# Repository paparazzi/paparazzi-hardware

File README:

#
#   $Id: README 6372 2010-11-07 00:50:29Z esden $
#   Copyright (C) 2004 Pascal Brisset, Antoine Drouin
#
# This file is part of paparazzi.
#
# paparazzi is free software; you can redistribute it and/or modify
# it under the terms of the GNU General Public License as published by
# the Free Software Foundation; either version 2, or (at your option)
# any later version.
#
# paparazzi is distributed in the hope that it will be useful,
# but WITHOUT ANY WARRANTY; without even the implied warranty of
# MERCHANTABILITY or FITNESS FOR A PARTICULAR PURPOSE.  See the
# GNU General Public License for more details.
#
# You should have received a copy of the GNU General Public License
# along with paparazzi; see the file COPYING.  If not, write to
# the Free Software Foundation, 59 Temple Place - Suite 330,
# Boston, MA 02111-1307, USA.  
# 

License:
--------
All PCB CAD files are released under GNU General Public License version 2 or
newer if not stated otherwise.

Older revisions:
----------------
This is a cleaned up repository that does not contain all the history of the
files. For older revisions please check the SVN repository on Savannah:
http://svn.savannah.nongnu.org/viewvc/paparazzi-hardware/trunk/?root=paparazzi

Techno:
-------
PCBs are 4 layers boards.
  They can be ordered from companies like eurocircuits (www.eurocircuits.com).
  I solder the components with a fine temperatue controlled iron. The IMU board 
  contains BGA gyros which will require some sort hot hot air method.

Tools:
  This files are produced using Eagle (www.cadsoft.de) version 4.11 for Linux.
  gerbmerge (http://claymore.engineer.gvsu.edu/~steriana/Python/gerbmerge/) is a
  free gerber panelisation tool. gerbv (http://gerbv.sourceforge.net) is a free
  gerber viewer. eagle3d ( http://www.matwei.de/doku.php?id=en:eagle3d:eagle3d )
  is a tool that allows generation of povray views of the boards.

Outputs:
  We use the eagle batch CAM processor to generate various outputs.
  type "make gerber" to generate gerber.
  type "make printable" to generate postscript and pdf. 
  they will be put in a printable subdirectory in each subdirectory. 

Directory content:
------------------
panel: 
  Contains configuration files used in conjunction with gerbmerge to produce a pannel
  to be sent to the PCB manufacturer (eurocircuits). A panel is a big PCB containing several smaller PCB.
  It allows you to choose which boards you want for your particular system.

controller: 
  This are the paparazzi controller boards.

sensors:

tools:

lib: 
  contains eagle library parts for components not found in the standard eagle library.

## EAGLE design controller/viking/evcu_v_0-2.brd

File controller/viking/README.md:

# Viking Motorsports Engine Control Unit

The latest version is `ECU v1.0` which corresponds to `v_0.2` board files.  More info can be found in https://wiki.paparazziuav.org/wiki/VMS_ECU

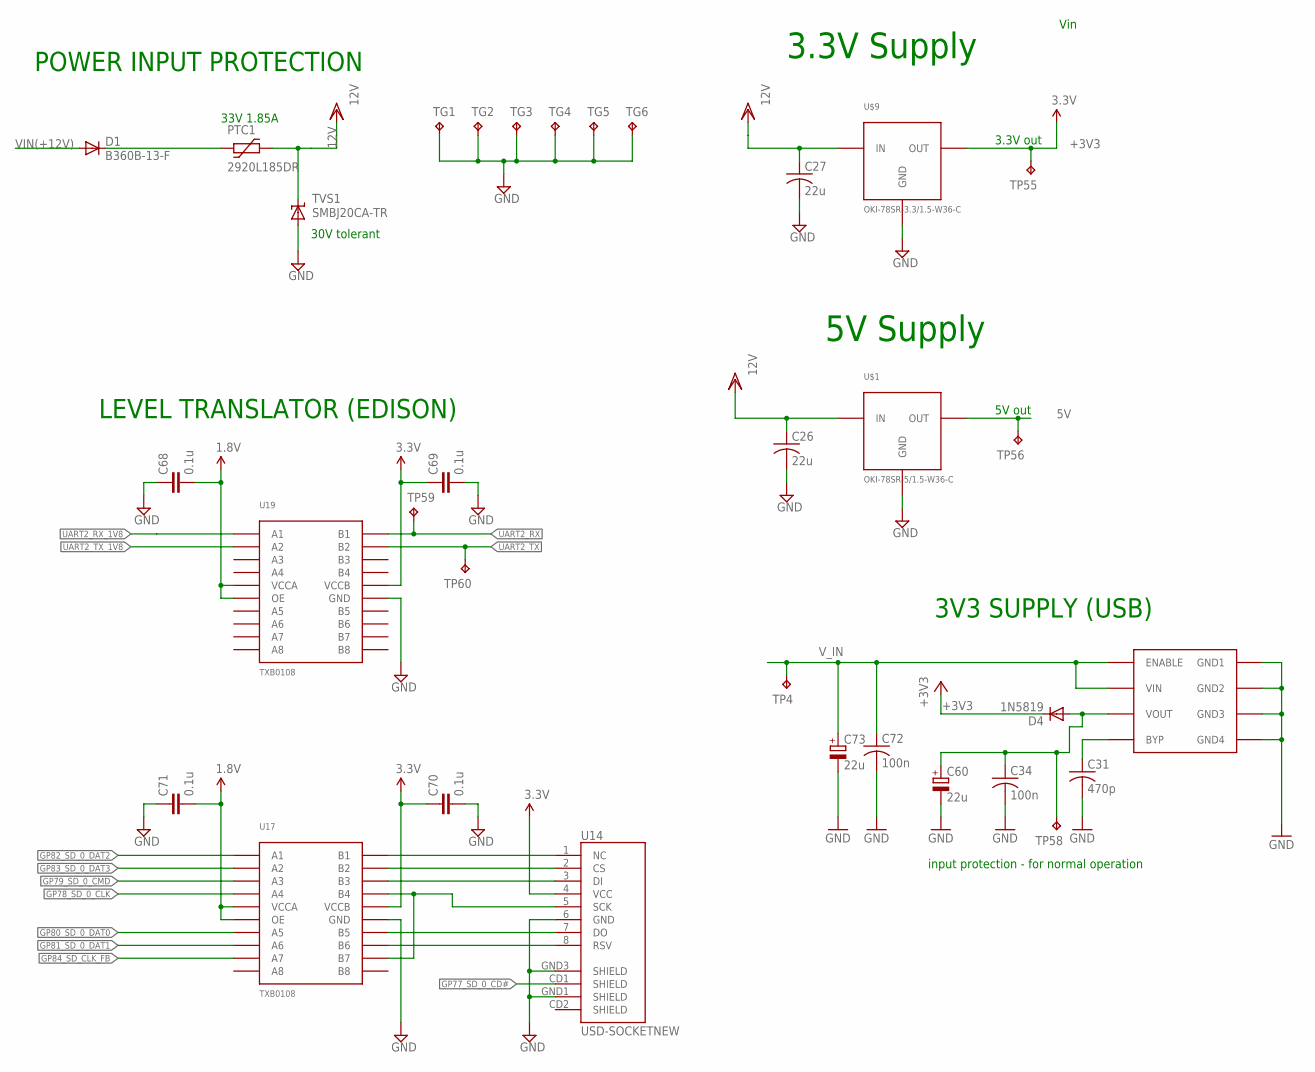
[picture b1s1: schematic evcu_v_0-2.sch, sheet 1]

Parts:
C26, C27: 22u; C1206
C31: 470p; C0603; PARTNO CC0402KRX7R9BB471
C34: 100n; C0603; PARTNO C0603C104K5RACTU
C60, C73: 22u; 3528/B; PARTNO T491B226M016AT
C68, C69, C70, C71: 0.1u; C0603@1
C72: 100n; C0603; PARTNO LMK105BJ104KV-F
D1: B360B-13-F; SMB
D4: 1N5819; MICROMELF-R; PARTNO RB160SS-40T2R
PTC1: 2920L185DR; 2920L
TG1, TG2, TG3, TG4, TG5, TG6: TPB1,27; B1,27
TP4, TP55, TP56, TP58, TP59, TP60: TPB1,27; B1,27
TVS1: SMBJ20CA-TR; SMBJ; PARTNO SM30T35AY
U14: USD-SOCKETNEW; MICRO-SD-SOCKET-PP
U17, U19: TXB0108; TSSOP20
U$1: OKI-78SR-5/1.5-W36-C; OKI-78SR
U$9: OKI-78SR-3.3/1.5-W36-C; OKI-78SR
VREG1: MIC5209; SOIC8; PARTNO MIC5209-3.3YM

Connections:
5V: TP56.TP, U$1.P3 (OUT); also elsewhere on the board
12V: C26.1, C27.1, PTC1.P$2 (2), TVS1.C, U$1.P1 (IN), U$9.P1 (IN); also elsewhere on the board
+1V8: C68.2, C71.2, U17.2 (VCCA), U17.10 (OE), U19.2 (VCCA), U19.10 (OE); also elsewhere on the board
+3V3: C69.1, C70.1, D4.C, TP55.TP, U14.4 (VCC), U17.19 (VCCB), U19.19 (VCCB), U$9.P3 (OUT); also elsewhere on the board
GND: C26.2, C27.2, C31.2, C34.2, C60.-, C68.1, C69.2, C70.2, C71.1, C72.2, C73.-, TG1.TP, TG2.TP, TG3.TP, TG4.TP, TG5.TP, TG6.TP, TVS1.A, U14.6 (GND), U14.GND1 (SHIELD), U14.GND3 (SHIELD), U17.11 (GND), U19.11 (GND), U$1.P2 (GND), U$9.P2 (GND), VREG1.5 (GND4), VREG1.6 (GND3), VREG1.7 (GND2), VREG1.8 (GND1); also elsewhere on the board
GP77_SD_0_CD#: U14.CD1 (SHIELD); also elsewhere on the board
GP78_SD_0_CLK: U17.5 (A4); also elsewhere on the board
GP79_SD_0_CMD: U17.4 (A3); also elsewhere on the board
GP80_SD_0_DAT0: U17.6 (A5); also elsewhere on the board
GP81_SD_0_DAT1: U17.7 (A6); also elsewhere on the board
GP82_SD_0_DAT2: U17.1 (A1); also elsewhere on the board
GP83_SD_0_DAT3: U17.3 (A2); also elsewhere on the board
GP84_SD_CLK_FB: U17.8 (A7); also elsewhere on the board
unnamed: U14.1 (NC), U17.20 (B1)
unnamed: U14.2 (CS), U17.18 (B2)
unnamed: U14.3 (DI), U17.17 (B3)
unnamed: U14.7 (DO), U17.15 (B5)
unnamed: U14.8 (RSV), U17.14 (B6)
unnamed: C31.1, VREG1.4 (BYP)
unnamed: C34.1, C60.+, D4.A, TP58.TP, VREG1.3 (VOUT)
unnamed: D1.C, PTC1.P$1 (1)
SCK: U14.5 (SCK), U17.13 (B7), U17.16 (B4)
UART2_RX: TP59.TP, U19.20 (B1); also elsewhere on the board
UART2_RX_1V8: U19.1 (A1); also elsewhere on the board
UART2_TX: TP60.TP, U19.18 (B2); also elsewhere on the board
UART2_TX_1V8: U19.3 (A2); also elsewhere on the board
VIN(+12V): D1.A; also elsewhere on the board
V_IN: C72.1, C73.+, TP4.TP, VREG1.1 (ENABLE), VREG1.2 (VIN); also elsewhere on the board

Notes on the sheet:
POWER INPUT PROTECTION
30V tolerant
3.3V out
Vin
3.3V Supply
5V out
5V Supply
33V 1.85A
LEVEL TRANSLATOR (EDISON)
3V3 SUPPLY (USB)
input protection - for normal operation

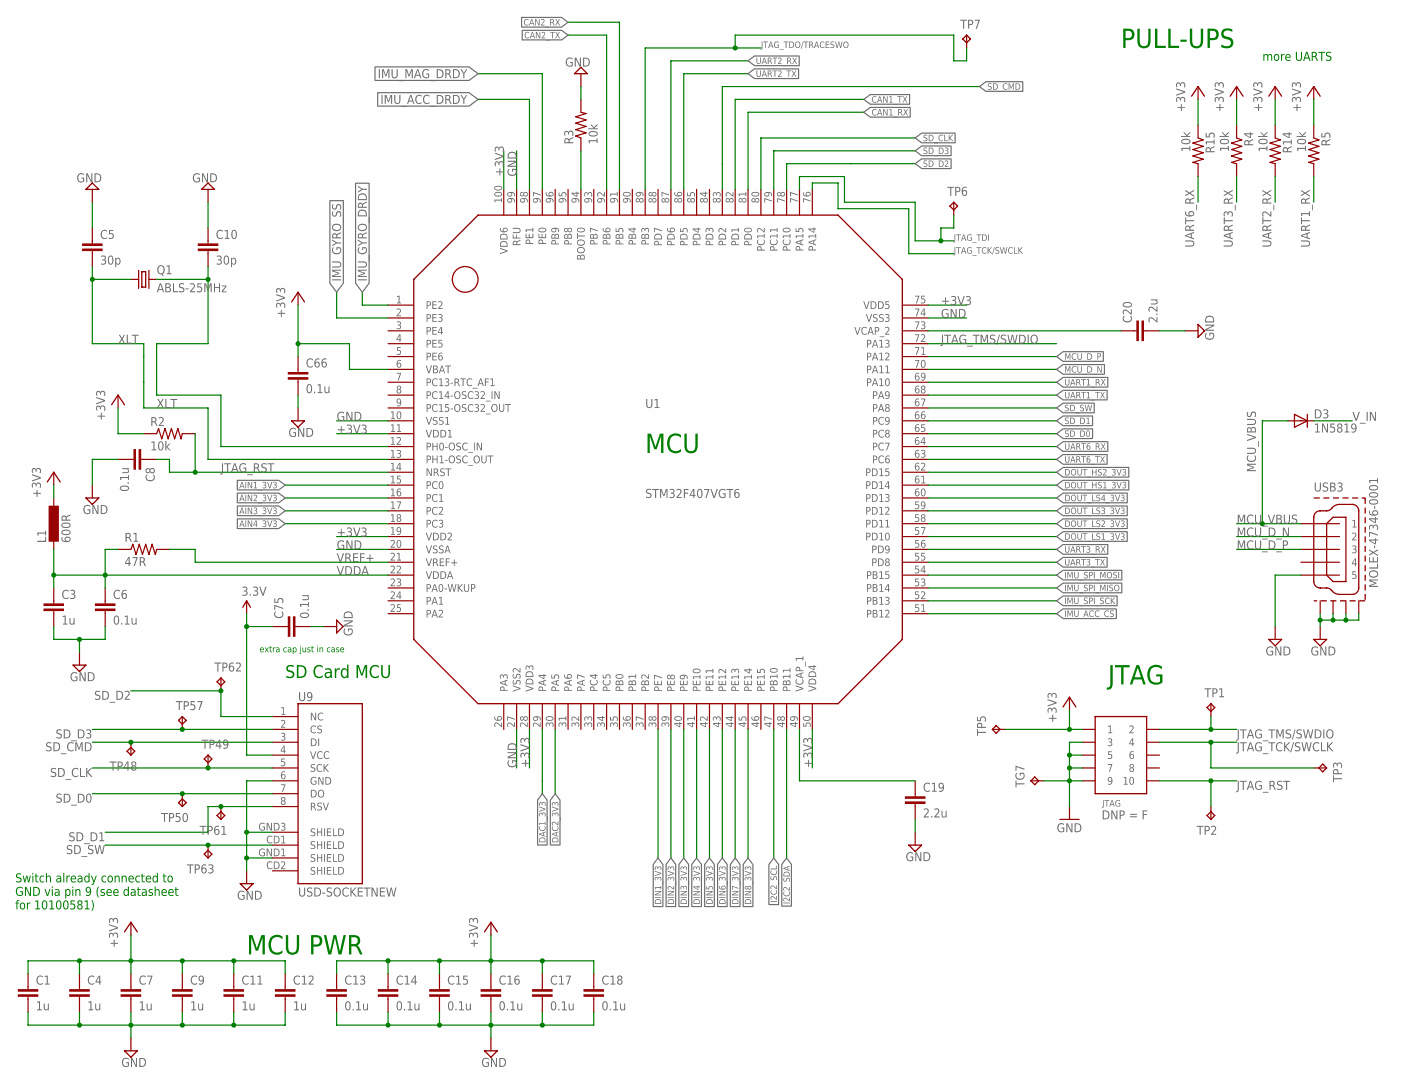
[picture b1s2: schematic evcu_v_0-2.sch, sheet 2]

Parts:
C1, C3, C4, C7, C9, C11, C12: 1u; C0603@1
C5, C10: 30p; C0603@1
C6, C8, C13, C14, C15, C16, C17, C18, C66, C75: 0.1u; C0603@1
C19, C20: 2.2u; C0603@1
D3: 1N5819; MICROMELF-R; PARTNO RB160SS-40T2R
JTAG: PIN_HDR_EDG_1.27MM_5-2; FTSH-105-DV; PARTNO conn-smd-0.05in-5-2
L1: 600R; 0603-IND
Q1: ABLS-25MHz; CSM-7X-DU
R1: 47R; R0603
R2, R3, R4, R5, R14, R15: 10k; R0603
TG7: TPB1,27; B1,27
TP1, TP2, TP3, TP5, TP6, TP7, TP48, TP49, TP50, TP57, TP61, TP62, TP63: TPB1,27; B1,27
U1: STM32F407VGT6; LQFP100
U9: USD-SOCKETNEW; MICRO-SD-SOCKET-PP
USB3: MOLEX-47346-0001; MOLEX-47364-0001

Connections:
+3V3: C1.1, C4.1, C7.1, C9.1, C11.1, C12.1, C13.1, C14.1, C15.1, C16.1, C17.1, C18.1, C66.1, C75.1, JTAG.1, L1.P$1 (1), R2.1, R4.1, R5.1, R14.1, R15.1, TP5.TP, U1.6 (VBAT), U1.11 (VDD1), U1.19 (VDD2), U1.28 (VDD3), U1.50 (VDD4), U1.75 (VDD5), U1.100 (VDD6), U9.4 (VCC); also elsewhere on the board
AIN1_3V3: U1.15 (PC0); also elsewhere on the board
AIN2_3V3: U1.16 (PC1); also elsewhere on the board
AIN3_3V3: U1.17 (PC2); also elsewhere on the board
AIN4_3V3: U1.18 (PC3); also elsewhere on the board
CAN1_RX: U1.81 (PD0); also elsewhere on the board
CAN1_TX: U1.82 (PD1); also elsewhere on the board
CAN2_RX: U1.91 (PB5); also elsewhere on the board
CAN2_TX: U1.92 (PB6); also elsewhere on the board
DAC1_3V3: U1.29 (PA4); also elsewhere on the board
DAC2_3V3: U1.30 (PA5); also elsewhere on the board
DIN1_3V3: U1.38 (PE7); also elsewhere on the board
DIN2_3V3: U1.39 (PE8); also elsewhere on the board
DIN3_3V3: U1.40 (PE9); also elsewhere on the board
DIN4_3V3: U1.41 (PE10); also elsewhere on the board
DIN5_3V3: U1.42 (PE11); also elsewhere on the board
DIN6_3V3: U1.43 (PE12); also elsewhere on the board
DIN7_3V3: U1.44 (PE13); also elsewhere on the board
DIN8_3V3: U1.45 (PE14); also elsewhere on the board
DOUT_HS1_3V3: U1.61 (PD14); also elsewhere on the board
DOUT_HS2_3V3: U1.62 (PD15); also elsewhere on the board
DOUT_LS1_3V3: U1.57 (PD10); also elsewhere on the board
DOUT_LS2_3V3: U1.58 (PD11); also elsewhere on the board
DOUT_LS3_3V3: U1.59 (PD12); also elsewhere on the board
DOUT_LS4_3V3: U1.60 (PD13); also elsewhere on the board
GND: C1.2, C3.2, C4.2, C5.1, C6.2, C7.2, C8.2, C9.2, C10.1, C11.2, C12.2, C13.2, C14.2, C15.2, C16.2, C17.2, C18.2, C19.2, C20.2, C66.2, C75.2, JTAG.3, JTAG.5, JTAG.7, JTAG.9, R3.2, TG7.TP, U1.10 (VSS1), U1.20 (VSSA), U1.27 (VSS2), U1.74 (VSS3), U1.99 (RFU), U9.6 (GND), U9.GND1 (SHIELD), U9.GND3 (SHIELD), USB3.5, USB3.GND1, USB3.GND2, USB3.GND3, USB3.GND4; also elsewhere on the board
I2C2_SCL: U1.47 (PB10); also elsewhere on the board
I2C2_SDA: U1.48 (PB11); also elsewhere on the board
IMU_ACC_CS: U1.51 (PB12); also elsewhere on the board
IMU_ACC_DRDY: U1.98 (PE1); also elsewhere on the board
IMU_GYRO_DRDY: U1.1 (PE2); also elsewhere on the board
IMU_GYRO_SS: U1.2 (PE3); also elsewhere on the board
IMU_MAG_DRDY: U1.97 (PE0); also elsewhere on the board
IMU_SPI_MISO: U1.53 (PB14); also elsewhere on the board
IMU_SPI_MOSI: U1.54 (PB15); also elsewhere on the board
IMU_SPI_SCK: U1.52 (PB13); also elsewhere on the board
JTAG_RST: C8.1, JTAG.10, R2.2, TP2.TP, U1.14 (NRST)
JTAG_TCK/SWCLK: JTAG.4, TP3.TP, U1.76 (PA14)
JTAG_TDI: TP6.TP, U1.77 (PA15)
JTAG_TDO/TRACESWO: TP7.TP, U1.89 (PB3)
JTAG_TMS/SWDIO: JTAG.2, TP1.TP, U1.72 (PA13)
MCU_D_N: U1.70 (PA11), USB3.2
MCU_D_P: U1.71 (PA12), USB3.3
MCU_VBUS: D3.A, USB3.1
unnamed: C19.1, U1.49 (VCAP_1)
unnamed: C20.1, U1.73 (VCAP_2)
unnamed: C10.2, Q1.2, U1.12 (PH0-OSC_IN)
unnamed: R3.1, U1.94 (BOOT0)
SD_CLK: TP49.TP, U1.80 (PC12), U9.5 (SCK)
SD_CMD: TP48.TP, U1.83 (PD2), U9.3 (DI)
SD_D0: TP50.TP, U1.65 (PC8), U9.7 (DO)
SD_D1: TP61.TP, U1.66 (PC9), U9.8 (RSV)
SD_D2: TP62.TP, U1.78 (PC10), U9.1 (NC)
SD_D3: TP57.TP, U1.79 (PC11), U9.2 (CS)
SD_SW: TP63.TP, U1.67 (PA8), U9.CD1 (SHIELD)
UART1_RX: R5.2, U1.69 (PA10); also elsewhere on the board
UART1_TX: U1.68 (PA9); also elsewhere on the board
UART2_RX: R14.2, U1.87 (PD6); also elsewhere on the board
UART2_TX: U1.86 (PD5); also elsewhere on the board
UART3_RX: R4.2, U1.56 (PD9); also elsewhere on the board
UART3_TX: U1.55 (PD8); also elsewhere on the board
UART6_RX: R15.2, U1.64 (PC7); also elsewhere on the board
UART6_TX: U1.63 (PC6); also elsewhere on the board
VDDA: C3.1, C6.1, L1.P$2 (2), R1.1, U1.22 (VDDA)
VREF+: R1.2, U1.21 (VREF+)
V_IN: D3.C; also elsewhere on the board
XLT: C5.2, Q1.1, U1.13 (PH1-OSC_OUT)

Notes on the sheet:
JTAG
MCU
MCU PWR
PULL-UPS
more UARTS
SD Card MCU
Switch already connected to GND via pin 9 (see datasheet for 10100581)
extra cap just in case

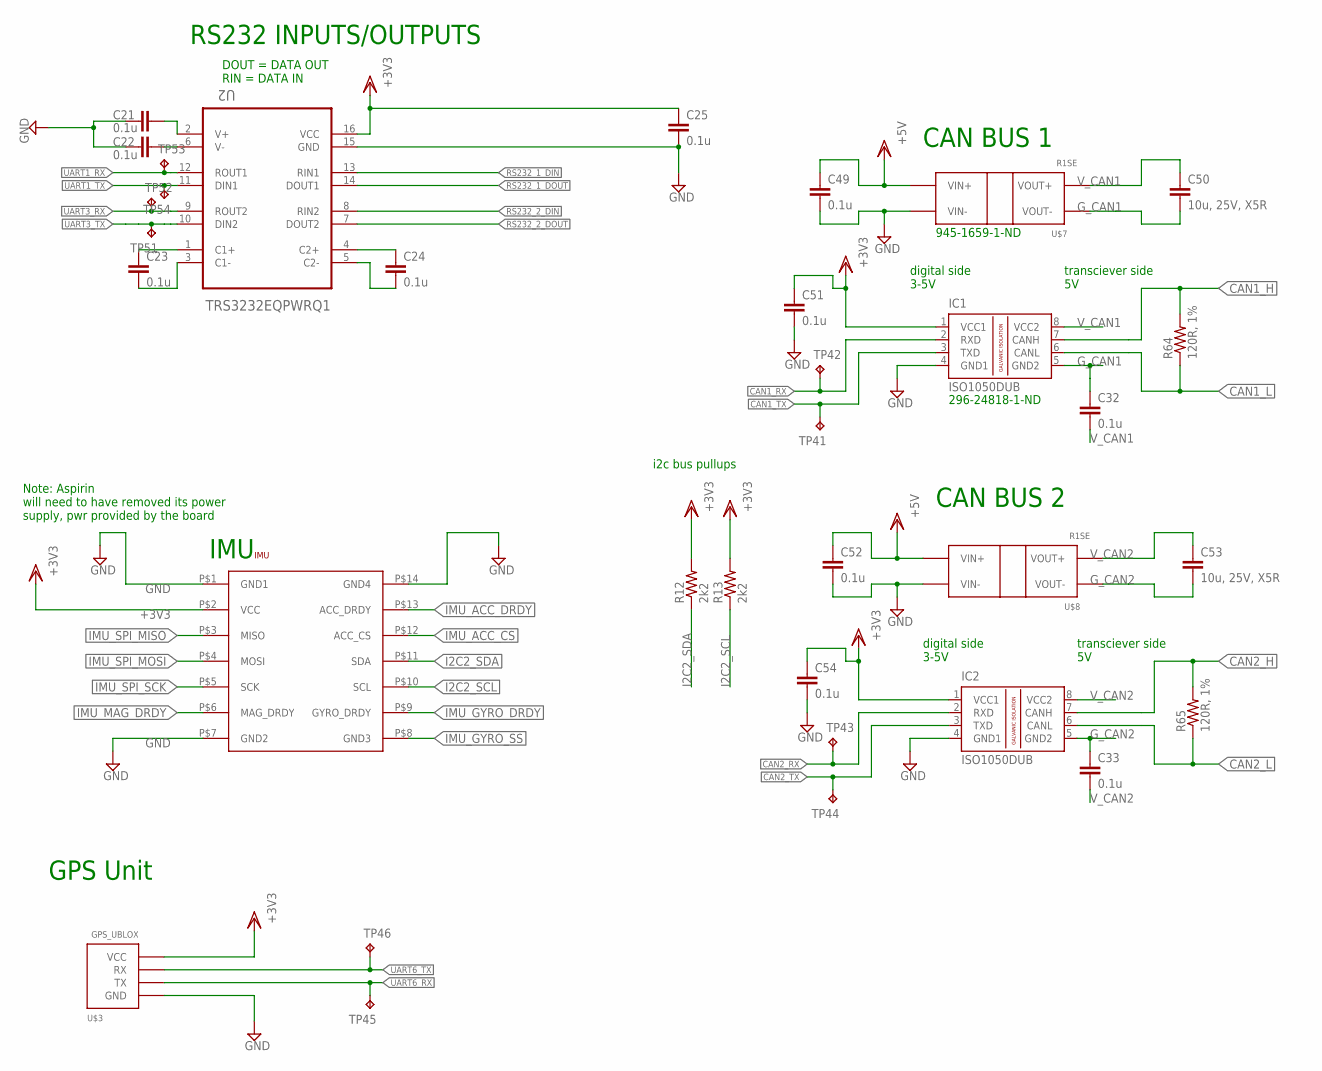
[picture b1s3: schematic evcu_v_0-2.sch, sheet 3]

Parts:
C21, C22, C23, C24, C25, C32, C33, C49, C51, C52, C54: 0.1u; C0603@1
C50, C53: 10u, 25V, X5R; C0603@1
IC1, IC2: ISO1050DUB; DUB-R-PDSO-G8
IMU: ASPIRIN; ASPIRIN_1; PARTNO ASP6000
R12, R13: 2k2; R0603
R64, R65: 120R, 1%; R0603
TP41, TP42, TP43, TP44, TP45, TP46, TP51, TP52, TP53, TP54: TPB1,27; B1,27
U2: TRS3232EQPWRQ1; SOP65P640X120-16N; DIGIKEY 296-24863-1-ND
U$3: GPS_UBLOX
U$7, U$8: R1SE

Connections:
5V: C49.1, C52.1, U$7.P2 (VIN+), U$8.P2 (VIN+); also elsewhere on the board
+3V3: C25.1, C51.1, C54.1, IC1.1 (VCC1), IC2.1 (VCC1), IMU.P$2 (VCC), R12.2, R13.2, U2.16 (VCC), U$3.VCC; also elsewhere on the board
CAN1_H: IC1.7 (CANH), R64.2; also elsewhere on the board
CAN1_L: IC1.6 (CANL), R64.1; also elsewhere on the board
CAN1_RX: IC1.2 (RXD), TP42.TP; also elsewhere on the board
CAN1_TX: IC1.3 (TXD), TP41.TP; also elsewhere on the board
CAN2_H: IC2.7 (CANH), R65.2; also elsewhere on the board
CAN2_L: IC2.6 (CANL), R65.1; also elsewhere on the board
CAN2_RX: IC2.2 (RXD), TP43.TP; also elsewhere on the board
CAN2_TX: IC2.3 (TXD), TP44.TP; also elsewhere on the board
GND: C21.1, C22.1, C25.2, C49.2, C51.2, C52.2, C54.2, IC1.4 (GND1), IC2.4 (GND1), IMU.P$1 (GND1), IMU.P$7 (GND2), IMU.P$14 (GND4), U2.15 (GND), U$3.GND, U$7.P1 (VIN-), U$8.P1 (VIN-); also elsewhere on the board
G_CAN1: C32.1, C50.2, IC1.5 (GND2), U$7.P4 (VOUT-)
G_CAN2: C33.1, C53.2, IC2.5 (GND2), U$8.P4 (VOUT-)
I2C2_SCL: IMU.P$10 (SCL), R13.1; also elsewhere on the board
I2C2_SDA: IMU.P$11 (SDA), R12.1; also elsewhere on the board
IMU_ACC_CS: IMU.P$12 (ACC_CS); also elsewhere on the board
IMU_ACC_DRDY: IMU.P$13 (ACC_DRDY); also elsewhere on the board
IMU_GYRO_DRDY: IMU.P$9 (GYRO_DRDY); also elsewhere on the board
IMU_GYRO_SS: IMU.P$8 (GND3); also elsewhere on the board
IMU_MAG_DRDY: IMU.P$6 (MAG_DRDY); also elsewhere on the board
IMU_SPI_MISO: IMU.P$3 (MISO); also elsewhere on the board
IMU_SPI_MOSI: IMU.P$4 (MOSI); also elsewhere on the board
IMU_SPI_SCK: IMU.P$5 (SCK); also elsewhere on the board
unnamed: C24.1, U2.4 (C2+)
unnamed: C24.2, U2.5 (C2-)
unnamed: C23.1, U2.1 (C1+)
unnamed: C23.2, U2.3 (C1-)
unnamed: C21.2, U2.2 (V+)
unnamed: C22.2, U2.6 (V-)
RS232_1_DIN: U2.13 (RIN1); also elsewhere on the board
RS232_1_DOUT: U2.14 (DOUT1); also elsewhere on the board
RS232_2_DIN: U2.8 (RIN2); also elsewhere on the board
RS232_2_DOUT: U2.7 (DOUT2); also elsewhere on the board
UART1_RX: TP53.TP, U2.12 (ROUT1); also elsewhere on the board
UART1_TX: TP54.TP, U2.11 (DIN1); also elsewhere on the board
UART3_RX: TP52.TP, U2.9 (ROUT2); also elsewhere on the board
UART3_TX: TP51.TP, U2.10 (DIN2); also elsewhere on the board
UART6_RX: TP45.TP, U$3.TX; also elsewhere on the board
UART6_TX: TP46.TP, U$3.RX; also elsewhere on the board
V_CAN1: C32.2, C50.1, IC1.8 (VCC2), U$7.P5 (VOUT+)
V_CAN2: C33.2, C53.1, IC2.8 (VCC2), U$8.P5 (VOUT+)

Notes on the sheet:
RS232 INPUTS/OUTPUTS
DOUT = DATA OUT RIN = DATA IN
IMU
GPS Unit
Note: Aspirin will need to have removed its power supply, pwr provided by the board
CAN BUS 1
digital side 3-5V
transciever side 5V
CAN BUS 2
945-1659-1-ND
296-24818-1-ND
i2c bus pullups

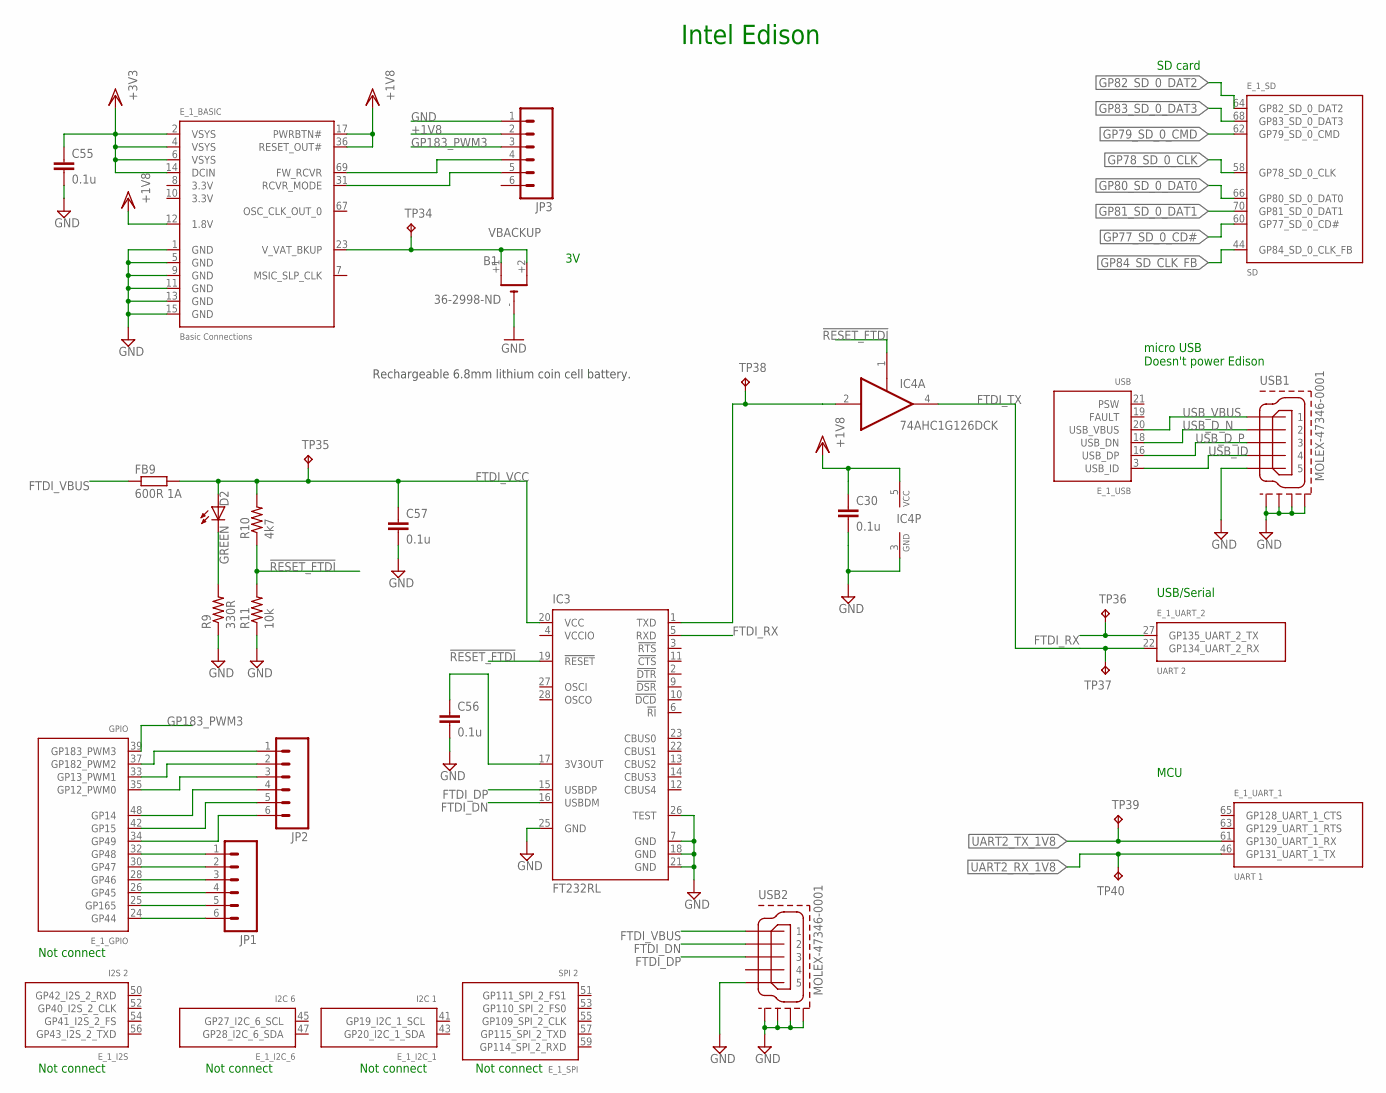
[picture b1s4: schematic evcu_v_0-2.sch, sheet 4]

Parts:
B1: 36-2998-ND; BATTERY_6.8MM-2998
C30, C55, C56, C57: 0.1u; C0603@1
D2: GREEN; D0603
E_1: EDISON_CONNECTOR_SEGMENTED; EDISON_DAUGHTER
FB9: 600R 1A; C0603
IC3: FT232RL; SSOP28
IC4: 74AHC1G126DCK; SC70-5
JP1, JP2, JP3: M06SIP; 1X06
R9: 330R; R0603
R10: 4k7; R0603
R11: 10k; R0603
TP34, TP35, TP36, TP37, TP38, TP39, TP40: TPB1,27; B1,27
USB1, USB2: MOLEX-47346-0001; MOLEX-47364-0001

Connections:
!RESET_FTDI: IC3.19 (!RESET), IC4.1 (OE), R10.1, R11.2
+1V8: C30.1, E_1.12 (1.8V), E_1.17 (PWRBTN#), E_1.36 (RESET_OUT#), IC4.5 (VCC), JP3.2; also elsewhere on the board
+3V3: C55.1, E_1.2 (VSYS), E_1.4 (VSYS), E_1.6 (VSYS), E_1.14 (DCIN); also elsewhere on the board
FTDI_DN: IC3.16 (USBDM), USB2.2
FTDI_DP: IC3.15 (USBDP), USB2.3
FTDI_RX: E_1.27 (GP135_UART_2_TX), IC3.5 (RXD), TP36.TP
FTDI_TX: E_1.22 (GP134_UART_2_RX), IC4.4 (O), TP37.TP
FTDI_VBUS: FB9.1, USB2.1
FTDI_VCC: C57.1, D2.A, FB9.2, IC3.20 (VCC), R10.2, TP35.TP
FW_RCVR: E_1.69 (FW_RCVR), JP3.4
GND: B1.-, C30.2, C55.2, C56.2, C57.2, E_1.1 (GND), E_1.5 (GND), E_1.9 (GND), E_1.11 (GND), E_1.13 (GND), E_1.15 (GND), IC3.7 (GND), IC3.18 (GND), IC3.21 (GND), IC3.25 (GND), IC3.26 (TEST), IC4.3 (GND), JP3.1, R9.1, R11.1, USB1.5, USB1.GND1, USB1.GND2, USB1.GND3, USB1.GND4, USB2.5, USB2.GND1, USB2.GND2, USB2.GND3, USB2.GND4; also elsewhere on the board
GP12: E_1.35 (GP12_PWM0), JP2.3
GP13: E_1.33 (GP13_PWM1), JP2.2
GP14: E_1.48 (GP14), JP2.4
GP15: E_1.42 (GP15), JP2.5
GP44: E_1.24 (GP44), JP1.6
GP45: E_1.26 (GP45), JP1.4
GP46: E_1.28 (GP46), JP1.3
GP47: E_1.30 (GP47), JP1.2
GP48: E_1.32 (GP48), JP1.1
GP49: E_1.34 (GP49), JP2.6
GP77_SD_0_CD#: E_1.60 (GP77_SD_0_CD#); also elsewhere on the board
GP78_SD_0_CLK: E_1.58 (GP78_SD_0_CLK); also elsewhere on the board
GP79_SD_0_CMD: E_1.62 (GP79_SD_0_CMD); also elsewhere on the board
GP80_SD_0_DAT0: E_1.66 (GP80_SD_0_DAT0); also elsewhere on the board
GP81_SD_0_DAT1: E_1.70 (GP81_SD_0_DAT1); also elsewhere on the board
GP82_SD_0_DAT2: E_1.64 (GP82_SD_0_DAT2); also elsewhere on the board
GP83_SD_0_DAT3: E_1.68 (GP83_SD_0_DAT3); also elsewhere on the board
GP84_SD_CLK_FB: E_1.44 (GP84_SD_0_CLK_FB); also elsewhere on the board
GP165: E_1.25 (GP165), JP1.5
GP182: E_1.37 (GP182_PWM2), JP2.1
GP183_PWM3: E_1.39 (GP183_PWM3), JP3.3
LED1_PWR: D2.C, R9.2
unnamed: C56.1, IC3.17 (3V3OUT)
unnamed: IC3.1 (TXD), IC4.2 (I), TP38.TP
RCVR_MODE: E_1.31 (RCVR_MODE), JP3.5
UART2_RX_1V8: E_1.46 (GP131_UART_1_TX), TP40.TP; also elsewhere on the board
UART2_TX_1V8: E_1.61 (GP130_UART_1_RX), TP39.TP; also elsewhere on the board
USB_D_N: E_1.18 (USB_DN), USB1.2
USB_D_P: E_1.16 (USB_DP), USB1.3
USB_ID: E_1.3 (USB_ID), USB1.4
USB_VBUS: E_1.20 (USB_VBUS), USB1.1
VBACKUP: B1.+1, B1.+2, E_1.23 (V_VAT_BKUP), TP34.TP
VCCIO: IC3.4 (VCCIO)

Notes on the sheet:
Intel Edison
micro USB Doesn't power Edison
Not connect
MCU
USB/Serial
SD card
Rechargeable 6.8mm lithium coin cell battery.

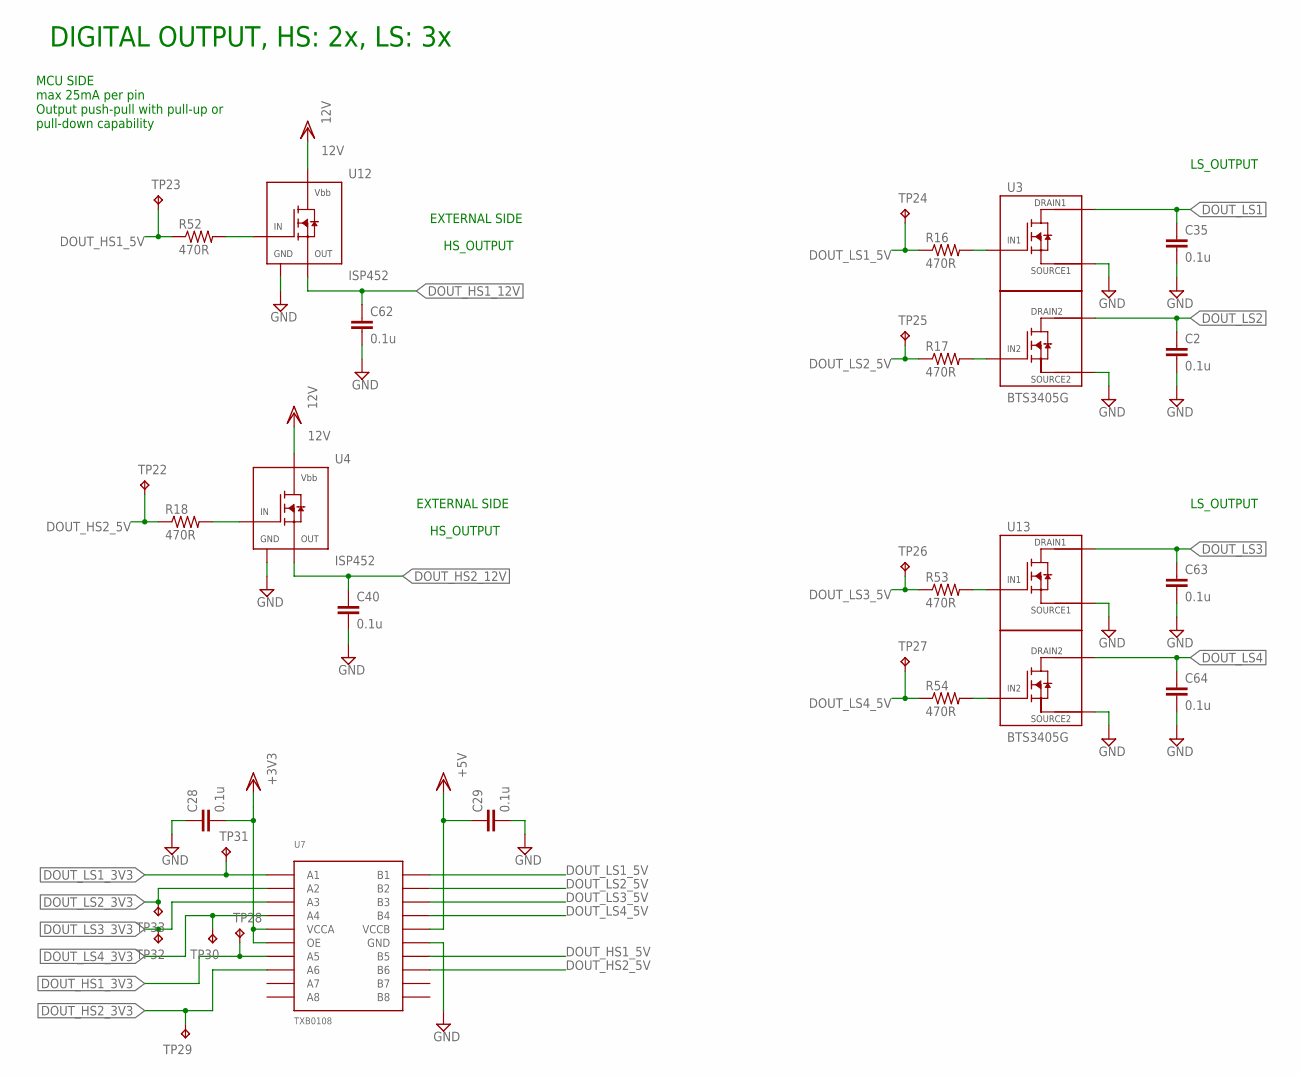
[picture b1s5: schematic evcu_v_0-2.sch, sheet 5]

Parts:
C2, C28, C29, C35, C40, C62, C63, C64: 0.1u; C0603@1
R16, R17, R18, R52, R53, R54: 470R; R0603
TP22, TP23, TP24, TP25, TP26, TP27, TP28, TP29, TP30, TP31, TP32, TP33: TPB1,27; B1,27
U3, U13: BTS3405G; SOIC8
U4, U12: ISP452; SOT223-W
U7: TXB0108; TSSOP20

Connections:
5V: C29.1, U7.19 (VCCB); also elsewhere on the board
12V: U4.4 (VBB), U12.4 (VBB); also elsewhere on the board
+3V3: C28.2, U7.2 (VCCA), U7.10 (OE); also elsewhere on the board
DOUT_HS1_3V3: TP28.TP, U7.6 (A5); also elsewhere on the board
DOUT_HS1_5V: R52.1, TP23.TP, U7.15 (B5)
DOUT_HS1_12V: C62.1, U12.1 (OUT); also elsewhere on the board
DOUT_HS2_3V3: TP29.TP, U7.7 (A6); also elsewhere on the board
DOUT_HS2_5V: R18.1, TP22.TP, U7.14 (B6)
DOUT_HS2_12V: C40.1, U4.1 (OUT); also elsewhere on the board
DOUT_LS1: C35.1, U3.7 (DRAIN1), U3.8 (DRAIN1); also elsewhere on the board
DOUT_LS1_3V3: TP31.TP, U7.1 (A1); also elsewhere on the board
DOUT_LS1_5V: R16.1, TP24.TP, U7.20 (B1)
DOUT_LS2: C2.1, U3.5 (DRAIN2), U3.6 (DRAIN2); also elsewhere on the board
DOUT_LS2_3V3: TP33.TP, U7.3 (A2); also elsewhere on the board
DOUT_LS2_5V: R17.1, TP25.TP, U7.18 (B2)
DOUT_LS3: C63.1, U13.7 (DRAIN1), U13.8 (DRAIN1); also elsewhere on the board
DOUT_LS3_3V3: TP32.TP, U7.4 (A3); also elsewhere on the board
DOUT_LS3_5V: R53.1, TP26.TP, U7.17 (B3)
DOUT_LS4: C64.1, U13.5 (DRAIN2), U13.6 (DRAIN2); also elsewhere on the board
DOUT_LS4_3V3: TP30.TP, U7.5 (A4); also elsewhere on the board
DOUT_LS4_5V: R54.1, TP27.TP, U7.16 (B4)
GND: C2.2, C28.1, C29.2, C35.2, C40.2, C62.2, C63.2, C64.2, U3.1 (SOURCE1), U3.3 (SOURCE2), U4.2 (GND), U7.11 (GND), U12.2 (GND), U13.1 (SOURCE1), U13.3 (SOURCE2); also elsewhere on the board
unnamed: R16.2, U3.2 (IN1)
unnamed: R17.2, U3.4 (IN2)
unnamed: R18.2, U4.3 (IN)
unnamed: R52.2, U12.3 (IN)
unnamed: R53.2, U13.2 (IN1)
unnamed: R54.2, U13.4 (IN2)

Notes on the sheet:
DIGITAL OUTPUT, HS: 2x, LS: 3x
MCU SIDE max 25mA per pin Output push-pull with pull-up or pull-down capability
EXTERNAL SIDE
HS_OUTPUT
LS_OUTPUT

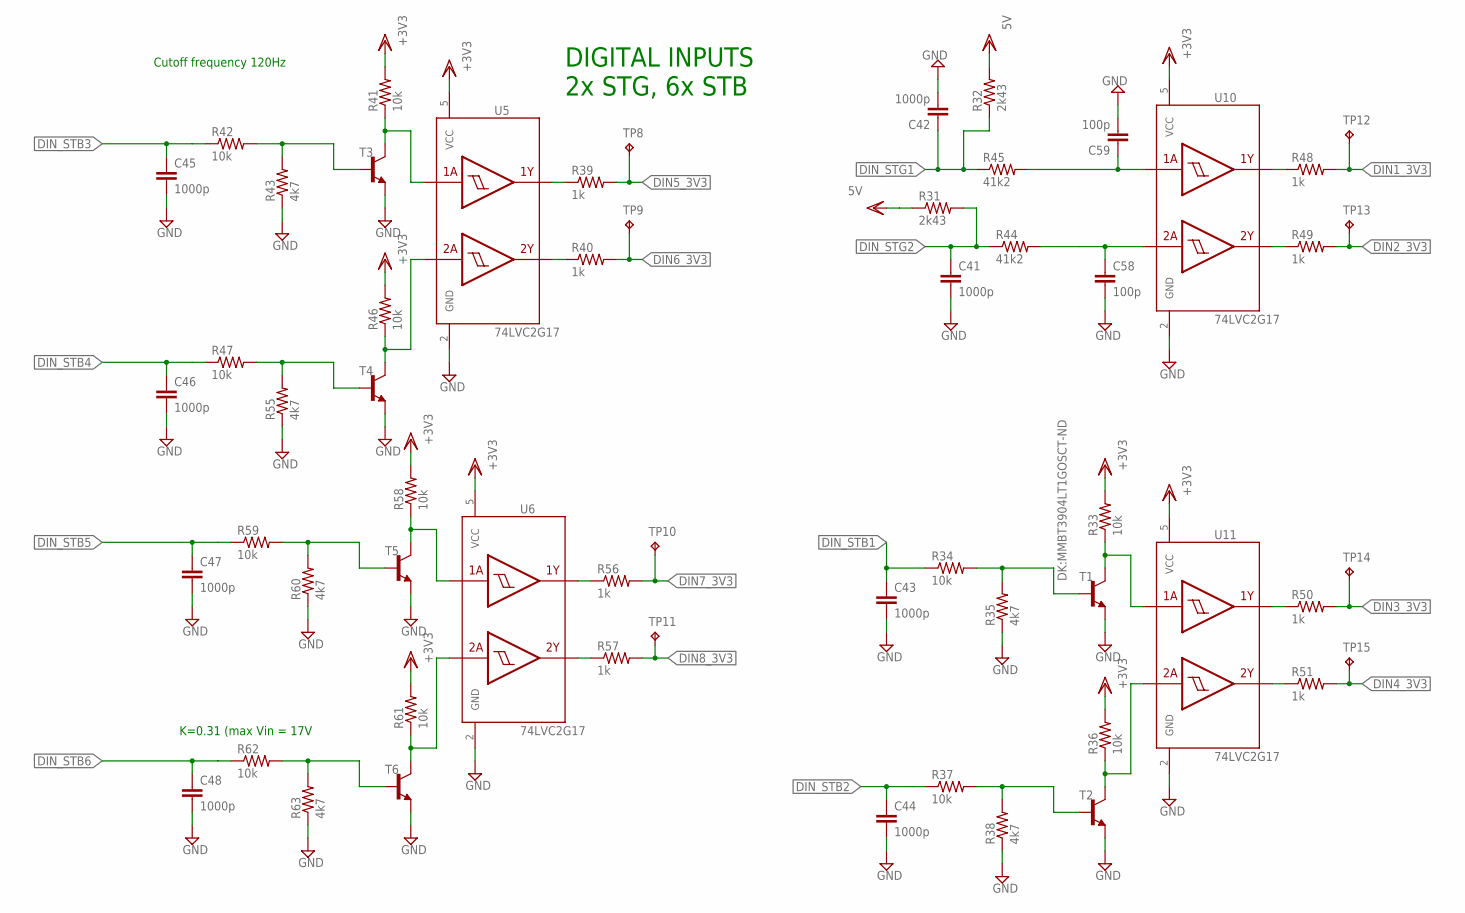
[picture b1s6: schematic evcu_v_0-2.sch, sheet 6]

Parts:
C41, C42, C43, C44, C45, C46, C47, C48: 1000p; C0603@1
C58, C59: 100p; C0603@1
R31, R32: 2k43; R0603
R33, R34, R36, R37, R41, R42, R46, R47, R58, R59, R61, R62: 10k; R0603
R35, R38, R43, R55, R60, R63: 4k7; R0603
R39, R40, R48, R49, R50, R51, R56, R57: 1k; R0603
R44, R45: 41k2; R0603
T1, T2, T3, T4, T5, T6: DK:MMBT3904LT1GOSCT-ND; SOT23-BEC
TP8, TP9, TP10, TP11, TP12, TP13, TP14, TP15: TPB1,27; B1,27
U5, U6, U10, U11: 74LVC2G17; SOT363_INFINEON

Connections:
5V: R31.1, R32.2; also elsewhere on the board
+3V3: R33.2, R36.2, R41.2, R46.2, R58.2, R61.2, U5.5 (VCC), U6.5 (VCC), U10.5 (VCC), U11.5 (VCC); also elsewhere on the board
DIN1_3V3: R48.2, TP12.TP; also elsewhere on the board
DIN2_3V3: R49.2, TP13.TP; also elsewhere on the board
DIN3_3V3: R50.2, TP14.TP; also elsewhere on the board
DIN4_3V3: R51.2, TP15.TP; also elsewhere on the board
DIN5_3V3: R39.2, TP8.TP; also elsewhere on the board
DIN6_3V3: R40.2, TP9.TP; also elsewhere on the board
DIN7_3V3: R56.2, TP10.TP; also elsewhere on the board
DIN8_3V3: R57.2, TP11.TP; also elsewhere on the board
DIN_STB1: C43.1, R34.1; also elsewhere on the board
DIN_STB2: C44.1, R37.1; also elsewhere on the board
DIN_STB3: C45.1, R42.1; also elsewhere on the board
DIN_STB4: C46.1, R47.1; also elsewhere on the board
DIN_STB5: C47.1, R59.1; also elsewhere on the board
DIN_STB6: C48.1, R62.1; also elsewhere on the board
DIN_STG1: C42.1, R32.1, R45.1; also elsewhere on the board
DIN_STG2: C41.1, R31.2, R44.1; also elsewhere on the board
GND: C41.2, C42.2, C43.2, C44.2, C45.2, C46.2, C47.2, C48.2, C58.2, C59.2, R35.1, R38.1, R43.1, R55.1, R60.1, R63.1, T1.E, T2.E, T3.E, T4.E, T5.E, T6.E, U5.2 (GND), U6.2 (GND), U10.2 (GND), U11.2 (GND); also elsewhere on the board
unnamed: R33.1, T1.C, U11.1 (1A)
unnamed: R36.1, T2.C, U11.3 (2A)
unnamed: R39.1, U5.6 (1Y)
unnamed: R40.1, U5.4 (2Y)
unnamed: R41.1, T3.C, U5.1 (1A)
unnamed: R46.1, T4.C, U5.3 (2A)
unnamed: R56.1, U6.6 (1Y)
unnamed: R57.1, U6.4 (2Y)
unnamed: R58.1, T5.C, U6.1 (1A)
unnamed: R61.1, T6.C, U6.3 (2A)
unnamed: R49.1, U10.4 (2Y)
unnamed: R48.1, U10.6 (1Y)
unnamed: R50.1, U11.6 (1Y)
unnamed: R51.1, U11.4 (2Y)
TVS1: C58.1, R44.2, U10.3 (2A)
TVS2: C59.1, R45.2, U10.1 (1A)
TVS3: R34.2, R35.2, T1.B
TVS4: R37.2, R38.2, T2.B
TVS5: R42.2, R43.2, T3.B
TVS6: R47.2, R55.2, T4.B
TVS7: R59.2, R60.2, T5.B
TVS8: R62.2, R63.2, T6.B

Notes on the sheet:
DIGITAL INPUTS 2x STG, 6x STB
Cutoff frequency 120Hz
K=0.31 (max Vin = 17V

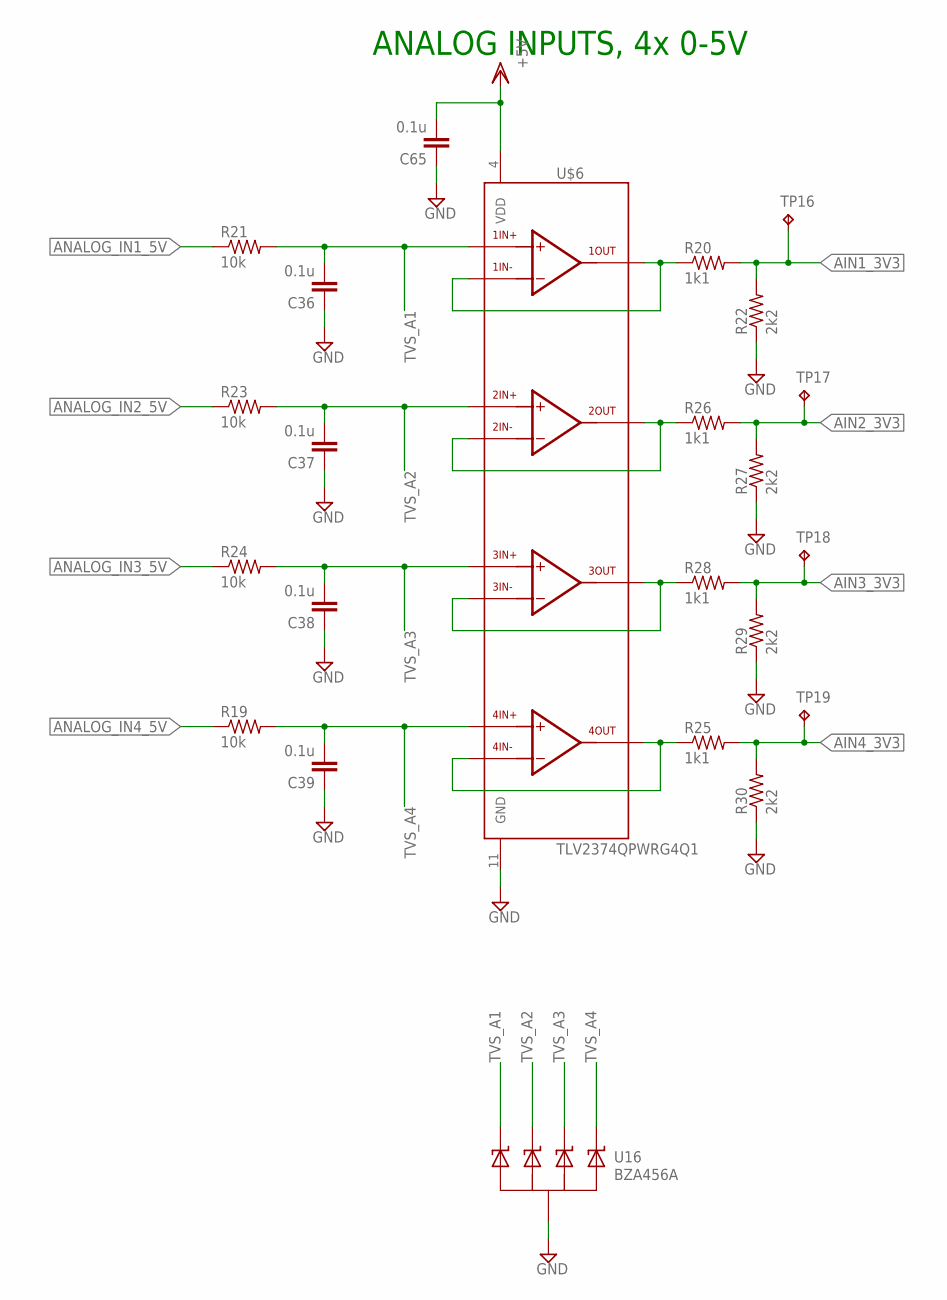
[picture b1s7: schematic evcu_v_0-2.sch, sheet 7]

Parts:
C36, C37, C38, C39, C65: 0.1u; C0603@1
R19, R21, R23, R24: 10k; R0603
R20, R25, R26, R28: 1k1; R0603
R22, R27, R29, R30: 2k2; R0603
TP16, TP17, TP18, TP19: TPB1,27; B1,27
U16: BZA456A; SOT457R_PHILIPS
U$6: TLV2374QPWRG4Q1; TSSOP14

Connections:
5V: C65.2, U$6.4 (VDD); also elsewhere on the board
AIN1_3V3: R20.2, R22.2, TP16.TP; also elsewhere on the board
AIN2_3V3: R26.2, R27.2, TP17.TP; also elsewhere on the board
AIN3_3V3: R28.2, R29.2, TP18.TP; also elsewhere on the board
AIN4_3V3: R25.2, R30.2, TP19.TP; also elsewhere on the board
ANALOG_IN1_5V: R21.1; also elsewhere on the board
ANALOG_IN2_5V: R23.1; also elsewhere on the board
ANALOG_IN3_5V: R24.1; also elsewhere on the board
ANALOG_IN4_5V: R19.1; also elsewhere on the board
GND: C36.1, C37.1, C38.1, C39.1, C65.1, R22.1, R27.1, R29.1, R30.1, U16.2 (COM), U16.5 (COM), U$6.11 (GND); also elsewhere on the board
unnamed: R25.1, U$6.13, U$6.14
unnamed: R20.1, U$6.1, U$6.2
unnamed: R26.1, U$6.6, U$6.7
unnamed: R28.1, U$6.8, U$6.9
TVS_A1: C36.2, R21.2, U16.1 (C1), U$6.3
TVS_A2: C37.2, R23.2, U16.3 (C2), U$6.5
TVS_A3: C38.2, R24.2, U16.4 (C3), U$6.10
TVS_A4: C39.2, R19.2, U16.6 (C4), U$6.12

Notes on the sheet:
ANALOG INPUTS, 4x 0-5V

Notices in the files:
controller/lia/breakout_board/lia_breakout.brd:
Licensed under:
(C) 2010-2012 Piotr Esden-Tempski
controller/lisa_m/v2.0/lisa_m.sch:
(C) 2010-2011 Piotr Esden-Tempski
controller/lisa_m/v2.1/lisa_m.brd:
(C) 2014
(C) 2010-2015 Piotr Esden-Tempski
parts and their libraries:
SparkFun-Passives: Licensing: Creative Commons ShareAlike 4.0 International - https://creativecommons.org/licenses/by-sa/4.0
